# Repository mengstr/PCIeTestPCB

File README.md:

# PCIeTestPCB

A simple PCB to test the 30 cent PCIe connectors from Mouser (SKU 649-1001878410200TLF). The PCB should be 1.6 mm to fit the connector.\

The PCB is meant to be split into two parts. The bottom part have the edgeconnector and a small DIP prototype area. The top parts holds the PCIe connectors and all five of them should be chained together into a backplane using wires going to card to card forming a bus.

This is a bit tedious, but for a quick test it's fine for me. If/when I will use PCIe connectors in a real project I definitely will make a proper backplane where all connectors are placed on the same PCB. But I didn;t want to spend good money for a test board. :-)

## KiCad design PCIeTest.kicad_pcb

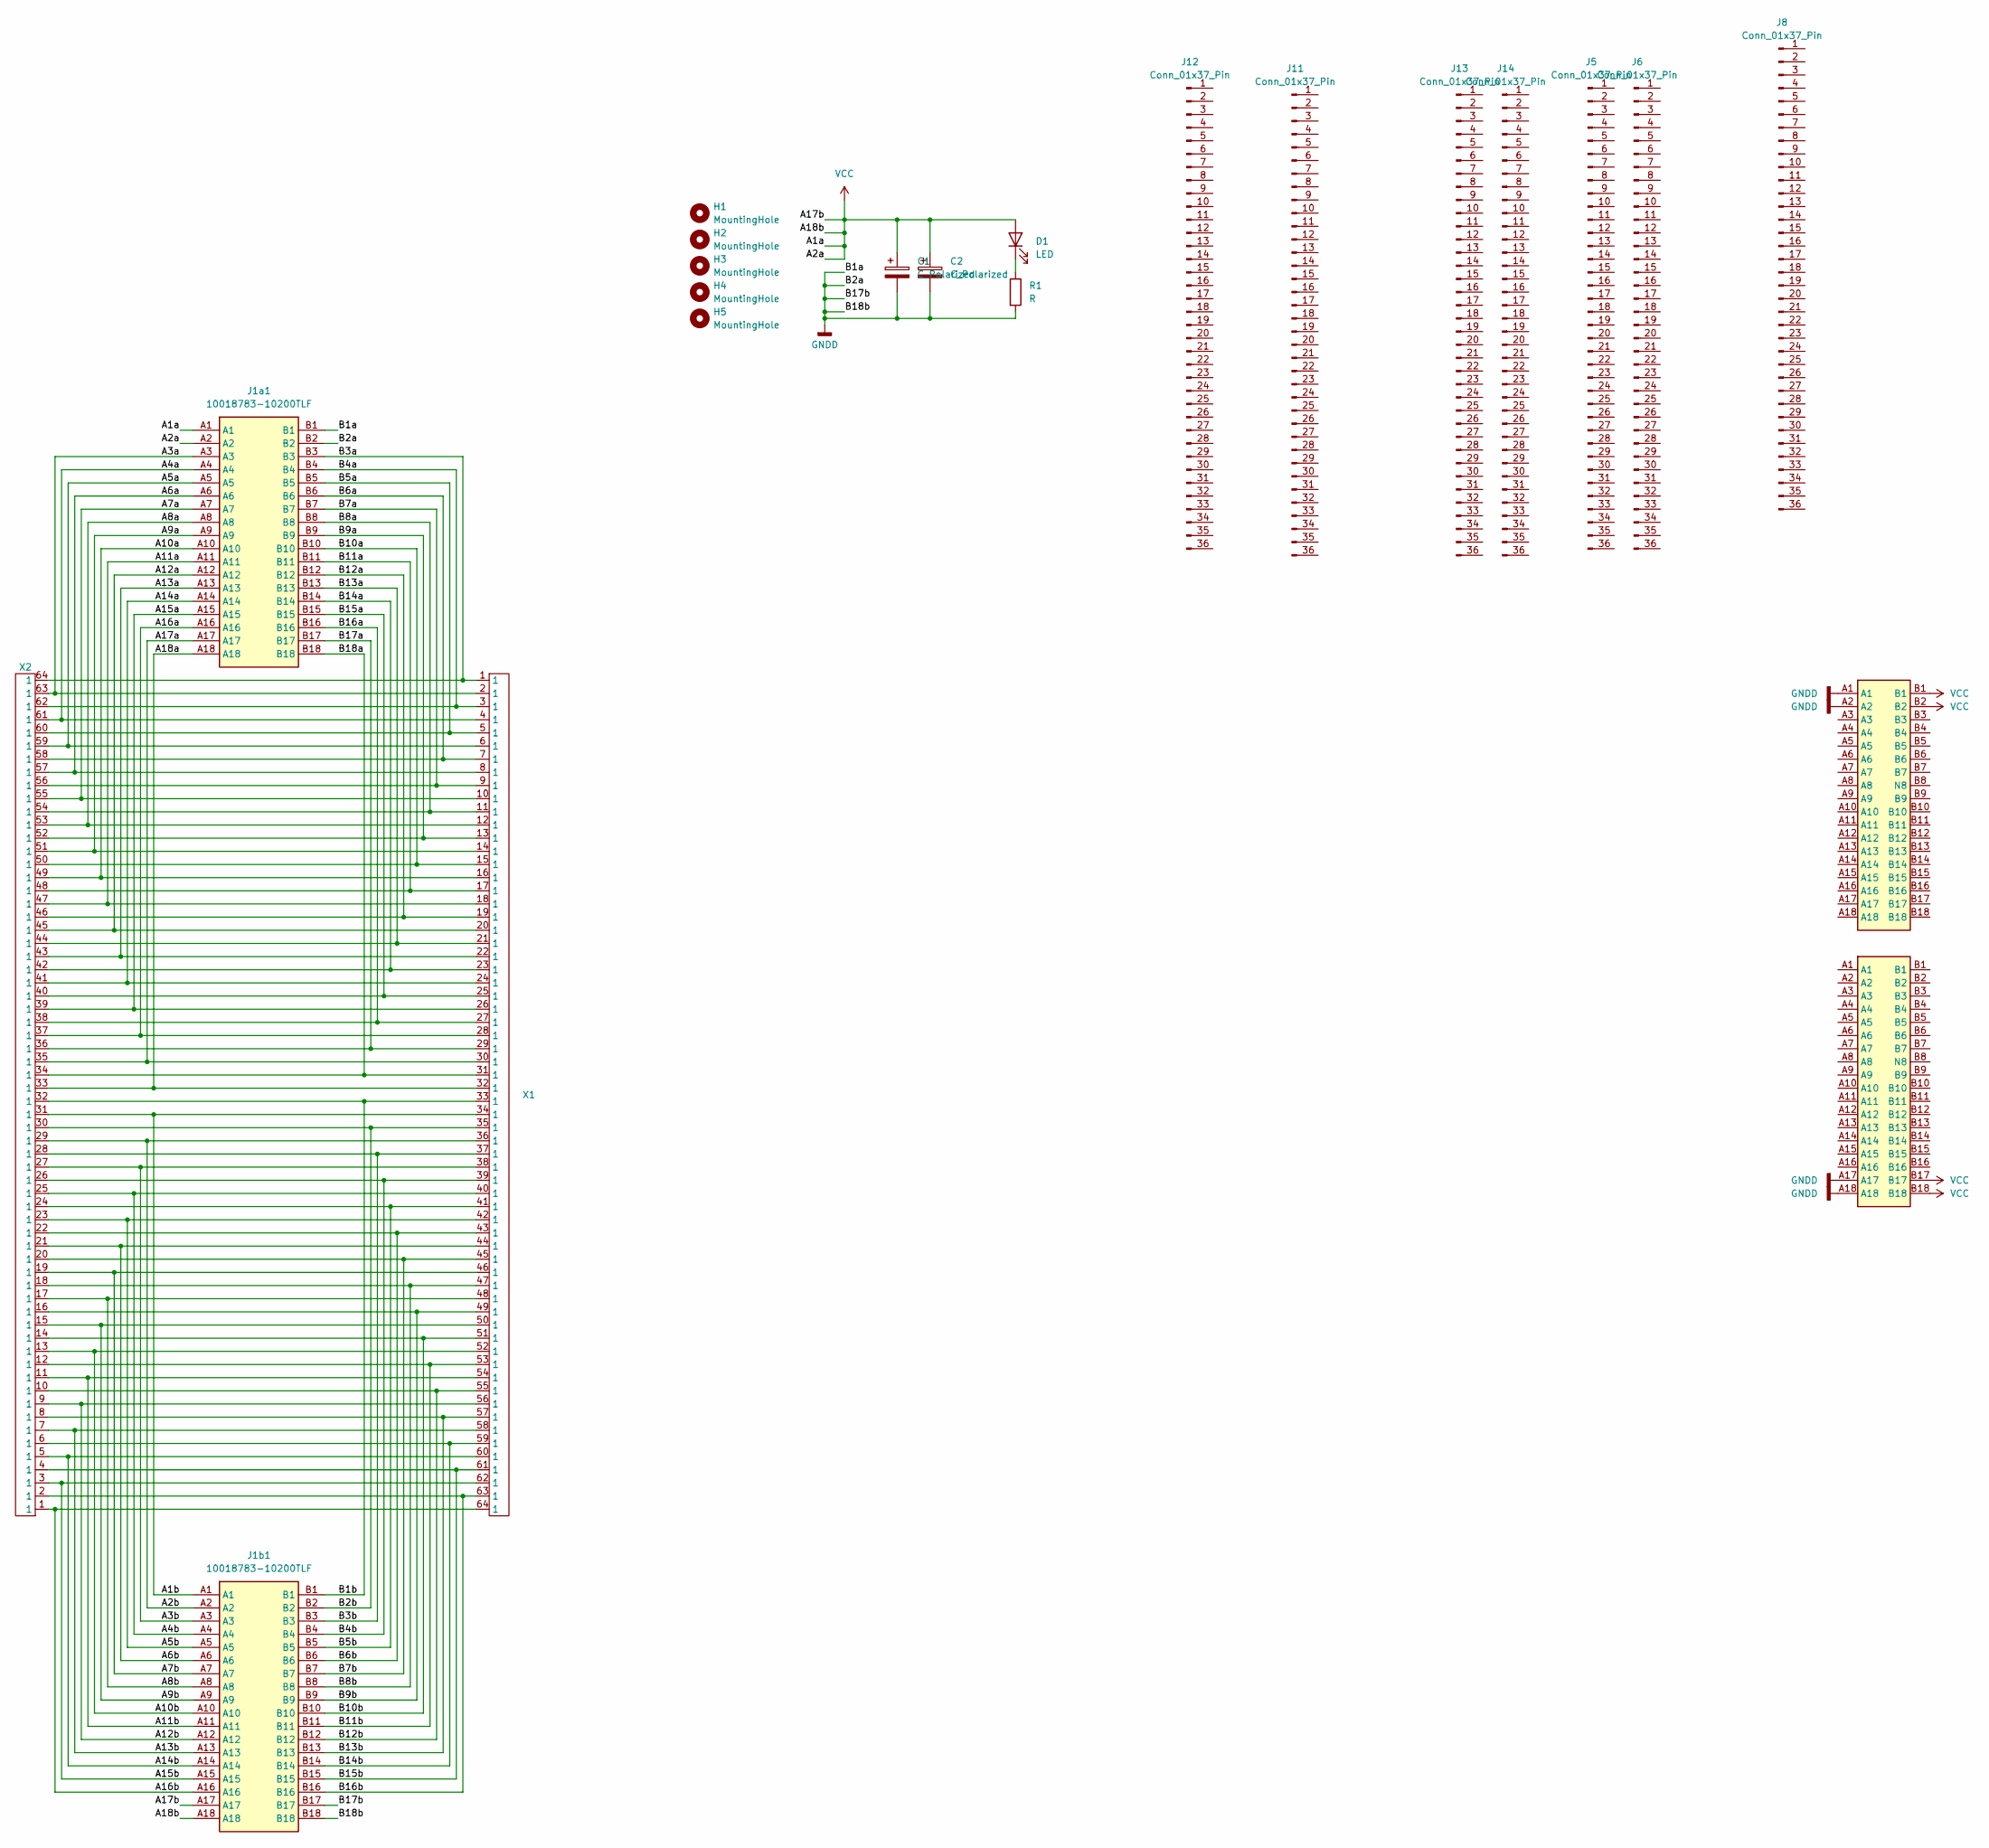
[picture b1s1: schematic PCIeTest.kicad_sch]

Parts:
C1, C2: C_Polarized; CP_Radial_D5.0mm_P2.50mm
D1: LED; LED_D3.0mm
H1, H2, H3, H4, H5: MountingHole; MountingHole_M2
J1a1, J1b1: 10018783-10200TLF; PCI-E36; Manufacturer_Part_Number 10018783-10200TLF; Mouser Part Number 649-1001878310200TLF
J5, J6, J8, J11, J12, J13, J14: Conn_01x37_Pin; WW37
JEa1: Bus_PCI_Express_x1; BUS_PCIexpress_x1
JEb1: Bus_PCI_Express_x1; BUS_PCIexpress_x1
R1: R; R_Axial_DIN0309_L9.0mm_D3.2mm_P12.70mm_Horizontal
X1, X2: PAD64-1.5_1.0

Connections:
/A1b: J1b1.A1, X1.34 (1), X2.31 (1)
/A2b: J1b1.A2, X1.36 (1), X2.29 (1)
/A3a: J1a1.A3, X1.2 (1), X2.63 (1)
/A3b: J1b1.A3, X1.38 (1), X2.27 (1)
/A4a: J1a1.A4, X1.4 (1), X2.61 (1)
/A4b: J1b1.A4, X1.40 (1), X2.25 (1)
/A5a: J1a1.A5, X1.6 (1), X2.59 (1)
/A5b: J1b1.A5, X1.42 (1), X2.23 (1)
/A6a: J1a1.A6, X1.8 (1), X2.57 (1)
/A6b: J1b1.A6, X1.44 (1), X2.21 (1)
/A7a: J1a1.A7, X1.10 (1), X2.55 (1)
/A7b: J1b1.A7, X1.46 (1), X2.19 (1)
/A8a: J1a1.A8, X1.12 (1), X2.53 (1)
/A8b: J1b1.A8, X1.48 (1), X2.17 (1)
/A9a: J1a1.A9, X1.14 (1), X2.51 (1)
/A9b: J1b1.A9, X1.50 (1), X2.15 (1)
/A10a: J1a1.A10, X1.16 (1), X2.49 (1)
/A10b: J1b1.A10, X1.52 (1), X2.13 (1)
/A11a: J1a1.A11, X1.18 (1), X2.47 (1)
/A11b: J1b1.A11, X1.54 (1), X2.11 (1)
/A12a: J1a1.A12, X1.20 (1), X2.45 (1)
/A12b: J1b1.A12, X1.56 (1), X2.9 (1)
/A13a: J1a1.A13, X1.22 (1), X2.43 (1)
/A13b: J1b1.A13, X1.58 (1), X2.7 (1)
/A14a: J1a1.A14, X1.24 (1), X2.41 (1)
/A14b: J1b1.A14, X1.60 (1), X2.5 (1)
/A15a: J1a1.A15, X1.26 (1), X2.39 (1)
/A15b: J1b1.A15, X1.62 (1), X2.3 (1)
/A16a: J1a1.A16, X1.28 (1), X2.37 (1)
/A16b: J1b1.A16, X1.64 (1), X2.1
/A17a: J1a1.A17, X1.30 (1), X2.35 (1)
/A18a: J1a1.A18, X1.32 (1), X2.33 (1)
/B1b: J1b1.B1, X1.33 (1), X2.32 (1)
/B2b: J1b1.B2, X1.35 (1), X2.30 (1)
/B3a: J1a1.B3, X1.1, X2.64 (1)
/B3b: J1b1.B3, X1.37 (1), X2.28 (1)
/B4a: J1a1.B4, X1.3 (1), X2.62 (1)
/B4b: J1b1.B4, X1.39 (1), X2.26 (1)
/B5a: J1a1.B5, X1.5 (1), X2.60 (1)
/B5b: J1b1.B5, X1.41 (1), X2.24 (1)
/B6a: J1a1.B6, X1.7 (1), X2.58 (1)
/B6b: J1b1.B6, X1.43 (1), X2.22 (1)
/B7a: J1a1.B7, X1.9 (1), X2.56 (1)
/B7b: J1b1.B7, X1.45 (1), X2.20 (1)
/B8a: J1a1.B8, X1.11 (1), X2.54 (1)
/B8b: J1b1.B8, X1.47 (1), X2.18 (1)
/B9a: J1a1.B9, X1.13 (1), X2.52 (1)
/B9b: J1b1.B9, X1.49 (1), X2.16 (1)
/B10a: J1a1.B10, X1.15 (1), X2.50 (1)
/B10b: J1b1.B10, X1.51 (1), X2.14 (1)
/B11a: J1a1.B11, X1.17 (1), X2.48 (1)
/B11b: J1b1.B11, X1.53 (1), X2.12 (1)
/B12a: J1a1.B12, X1.19 (1), X2.46 (1)
/B12b: J1b1.B12, X1.55 (1), X2.10 (1)
/B13a: J1a1.B13, X1.21 (1), X2.44 (1)
/B13b: J1b1.B13, X1.57 (1), X2.8 (1)
/B14a: J1a1.B14, X1.23 (1), X2.42 (1)
/B14b: J1b1.B14, X1.59 (1), X2.6 (1)
/B15a: J1a1.B15, X1.25 (1), X2.40 (1)
/B15b: J1b1.B15, X1.61 (1), X2.4 (1)
/B16a: J1a1.B16, X1.27 (1), X2.38 (1)
/B16b: J1b1.B16, X1.63 (1), X2.2 (1)
/B17a: J1a1.B17, X1.29 (1), X2.36 (1)
/B18a: J1a1.B18, X1.31 (1), X2.34 (1)
GNDD: C1.2, C2.2, J1a1.B1, J1a1.B2, J1b1.B17, J1b1.B18, JEa1.A1, JEa1.A2, JEb1.A17, JEb1.A18, R1.2
unnamed: D1.1 (K), R1.1
VCC: C1.1, C2.1, D1.2 (A), J1a1.A1, J1a1.A2, J1b1.A17, J1b1.A18, JEa1.B1, JEa1.B2, JEb1.B17, JEb1.B18

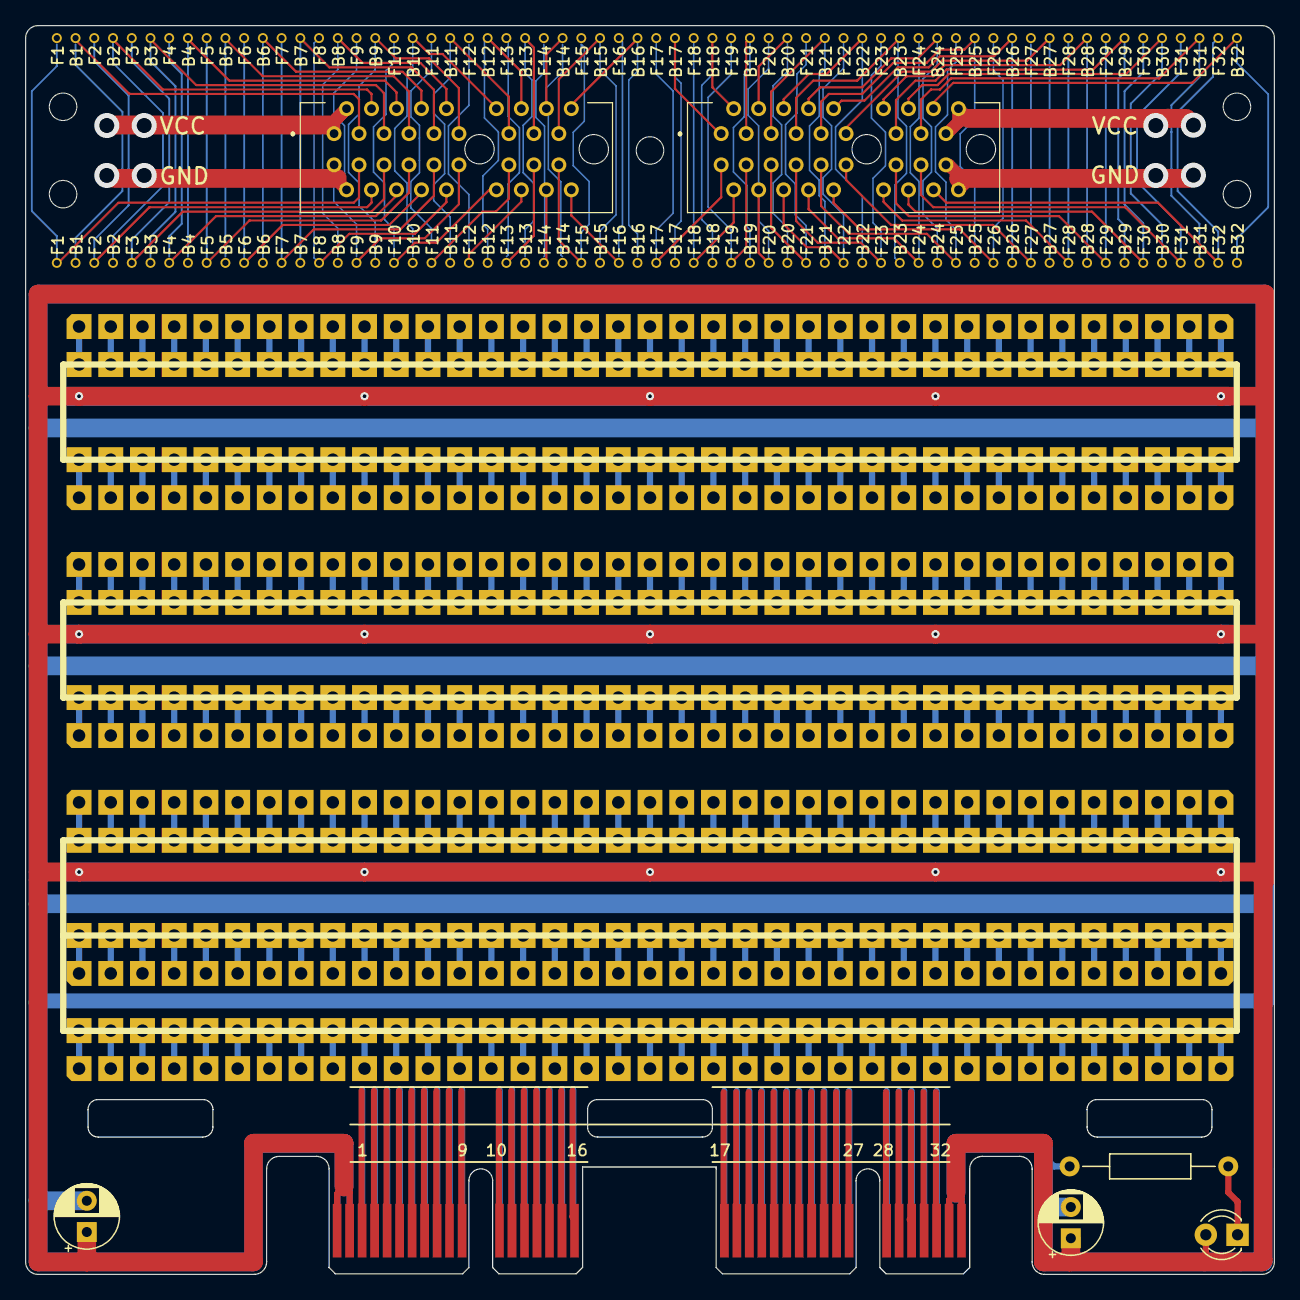
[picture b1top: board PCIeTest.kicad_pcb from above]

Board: 2 copper layers, 100.0 x 100.0 mm, 22 parts (0 on the bottom side), 67 nets.

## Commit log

2023-09-30 Sent to prod
2023-10-19 Add images
2023-10-19 Create LICENSE
